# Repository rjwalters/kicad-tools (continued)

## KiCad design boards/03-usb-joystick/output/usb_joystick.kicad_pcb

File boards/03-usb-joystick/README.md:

# USB Joystick Controller Demo

This demo demonstrates the kicad-tools autorouter by routing a USB game controller PCB
with mixed signal types: USB differential pairs, analog inputs, and digital I/O.

## Quick Start

```bash
# One-command build (recommended)
kct build boards/03-usb-joystick

# Or run specific steps
kct build boards/03-usb-joystick --step schematic
kct build boards/03-usb-joystick --step pcb
kct build boards/03-usb-joystick --step route
kct build boards/03-usb-joystick --step verify

# Preview what would happen
kct build boards/03-usb-joystick --dry-run
```

## Circuit Overview

```
                          +------------------+
    +--------+            |                  |
    | USB-C  |---D+/D--->| MCU (32-pin QFP) |<---[Y1 Crystal]
    |  J1    |---VBUS--->|                  |
    +--------+            |   ATmega32U4    |<---[C1-C4 Decoupling]
                          |                  |
                          +--------+---------+
                                   |
          +------------------------+------------------------+
          |            |           |           |            |
      +---+---+   +----+----+  +---+---+   +---+---+   +---+---+
      | JOY_X |   | JOY_Y   |  | BTN1  |   | BTN2  |   | BTN3  |
      +-------+   +---------+  +-------+   +-------+   +-------+
         Analog Joystick              Tactile Buttons
```

## Components

| Reference | Description | Footprint |
|-----------|-------------|-----------|
| U1 | Microcontroller (ATmega32U4-style) | TQFP-32 7x7mm |
| J1 | USB Type-C Connector | USB-C Receptacle |
| J2 | 2-axis Analog Joystick | 5-pin module |
| SW1-SW4 | Tactile Buttons | 6x6mm SMD |
| Y1 | 16MHz Crystal | HC49 Vertical |
| C1-C4 | Decoupling Capacitors (100nF) | 0402 SMD |

## Signal Types

This design demonstrates routing of different signal classes:

### USB Signals (High Priority)
- **USB_D+, USB_D-**: Differential pair, should be length-matched
- **VBUS**: 5V power from USB host
- **USB_CC1, USB_CC2**: Configuration channel for USB-C

### Analog Signals
- **JOY_X, JOY_Y**: Analog joystick axis outputs (0-VCC)
- **JOY_BTN**: Joystick button (active low)

### Digital Signals
- **BTN1-BTN4**: Button inputs (active low with GND)
- **XTAL1, XTAL2**: Crystal oscillator connections

### Power
- **VCC**: 3.3V/5V regulated power
- **GND**: Ground reference
- **VBUS**: USB 5V input

## Files

| File | Description |
|------|-------------|
| `generate_pcb.py` | Script to generate the unrouted PCB file |
| `generate_schematic.py` | Script to generate the schematic file |
| `route_demo.py` | Thin wrapper that delegates to `generate_design.py:route_pcb()` (Issue #3308) |
| `generate_design.py` | End-to-end design flow (schematic + PCB + route + export); owns the canonical routing recipe |
| `output/usb_joystick.kicad_sch` | Generated schematic |
| `output/usb_joystick.kicad_pcb` | Generated unrouted PCB |
| `output/usb_joystick_routed.kicad_pcb` | Routed PCB output |

## Advanced: Manual Build

For more control over individual steps, you can run Python scripts directly. See [Prerequisites](../README.md#prerequisites-for-manual-build) for environment setup.

### Step 1: Generate the Schematic

```bash
# From repository root (default output)
uv run python boards/03-usb-joystick/generate_schematic.py

# Or specify an output directory (auto-appends filename)
uv run python boards/03-usb-joystick/generate_schematic.py output/

# Or specify an explicit file path
uv run python boards/03-usb-joystick/generate_schematic.py output/usb_joystick.kicad_sch
```

Creates `output/usb_joystick.kicad_sch` with all components and wiring.

### Step 2: Generate the PCB

```bash
# From repository root
uv run python boards/03-usb-joystick/generate_pcb.py
```

Creates `output/usb_joystick.kicad_pcb` with all components placed and nets defined.

### Step 3: Run the Autorouter

```bash
# From repository root
uv run python boards/03-usb-joystick/route_demo.py
```

Issue #3308 (June 2026): `route_demo.py` is a thin wrapper that
delegates to `generate_design.py:route_pcb()`.  This guarantees the
demo recipe and the end-to-end build recipe share a single
implementation -- they cannot drift again.  `kct build --step route`
also invokes `route_demo.py` (see `_run_step_route` in
`src/kicad_tools/cli/build_cmd.py`), so all three entry points
(``route_demo.py``, ``kct build --step route``, ``generate_design.py``)
now produce the same routed output.

This:
1. Loads the unrouted PCB
2. Configures net classes (USB gets high priority)
3. Routes signal nets (power nets are skipped, assuming planes)
4. Saves the result to `output/usb_joystick_routed.kicad_pcb`

**Note:** This is a challenging routing problem with a dense 32-pin QFP and multiple
signal types. The autorouter demonstrates its capabilities but may not complete all
routes on a 2-layer board. This is realistic for complex designs requiring manual
intervention or additional layers.

### Step 4: View in KiCad (Optional)

Open `usb_joystick_routed.kicad_pcb` in KiCad to visualize the routes.

## Net Class Configuration

The demo configures net classes for priority-based routing:

```python
net_class_map = create_net_class_map(
    power_nets=["VCC", "VBUS", "GND"],  # Highest priority
    high_speed_nets=["USB_D+", "USB_D-"],  # USB differential pair
    clock_nets=["XTAL1", "XTAL2"],  # Crystal oscillator
)
```

This ensures:
1. Power nets route first (if not skipped)
2. USB differential pair routes early for best path
3. Crystal traces stay short
4. Button/joystick signals route last

## Design Considerations

### USB Routing
- D+ and D- should be routed as a differential pair
- Keep traces short and matched in length
- Avoid sharp bends (use 45-degree angles)

### Analog Signals
- JOY_X and JOY_Y carry analog voltages
- Keep away from high-speed digital signals
- Consider guard traces if noise is an issue

### Crystal Routing
- XTAL1 and XTAL2 should be short
- Place crystal close to MCU pins
- Avoid routing other signals under crystal

### Decoupling Capacitors
- C1-C3 placed close to MCU VCC pins
- C4 on VBUS near USB connector
- Short traces to GND plane

## Customization

### Change Design Rules

```python
rules = DesignRules(
    grid_resolution=0.25,  # Routing grid
    trace_width=0.25,  # Default trace width
    trace_clearance=0.15,  # Minimum clearance
    via_drill=0.3,  # Via drill diameter
    via_diameter=0.6,  # Via pad diameter
)
```

### Route Power Nets

By default, VCC/GND/VBUS are skipped (assuming copper pours). To route them:

```python
skip_nets = []  # Route everything
```

### Adjust Component Placement

Edit `generate_pcb.py` to modify:
- Board dimensions
- Component positions
- Pin assignments

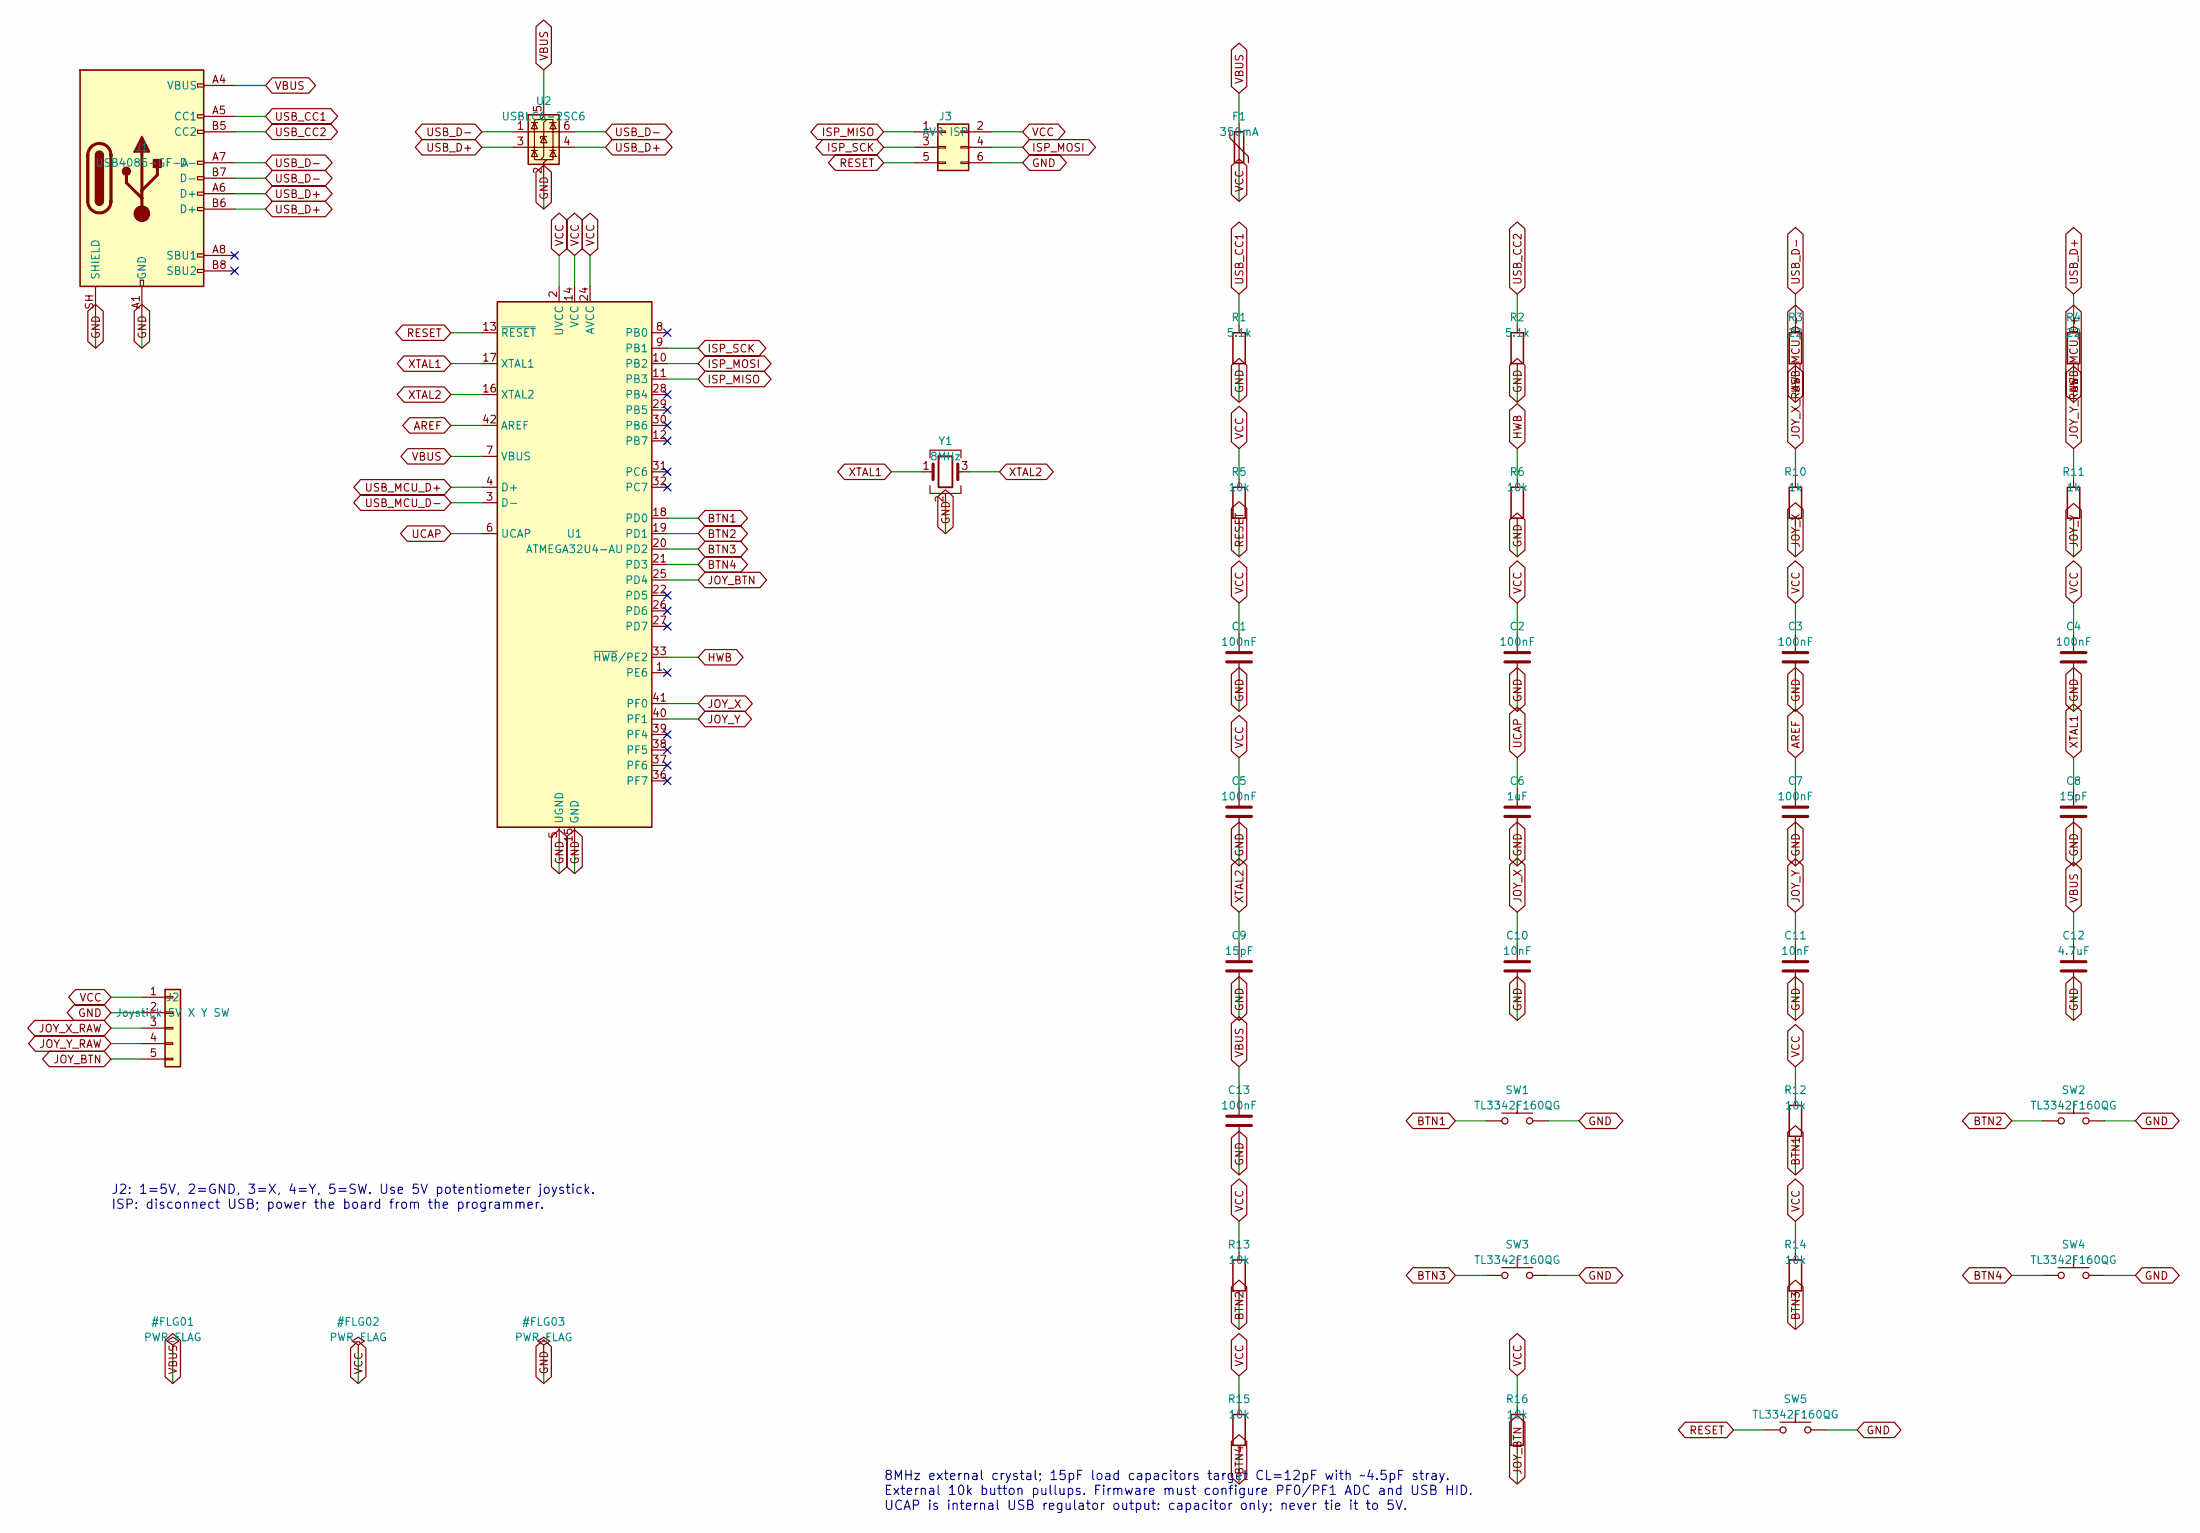
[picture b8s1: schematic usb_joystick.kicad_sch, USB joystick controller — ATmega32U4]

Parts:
C1, C2, C3, C4, C5, C7, C13: 100nF; C_0603_1608Metric; MPN GRM188R71C104KA01D; LCSC C45000
C6: 1uF; C_0603_1608Metric; MPN GRM188R71A105KA61D; LCSC C97888
C8, C9: 15pF; C_0603_1608Metric; MPN GRM1885C1H150JA01D; LCSC C71651
C10, C11: 10nF; C_0603_1608Metric; MPN GRM188R71H103KA01D; LCSC C77053
C12: 4.7uF; C_0603_1608Metric; MPN GRM188R61A475KE15D; LCSC C71633
F1: 350mA; Fuse_1206_3216Metric; MPN 1206L035/16YR; LCSC C126817
J1: USB4085-GF-A; USB_C_Receptacle_GCT_USB4085; MPN USB4085-GF-A; LCSC C7095263
J2: Joystick 5V X Y SW; JST_PH_S5B-PH-SM4-TB_1x05-1MP_P2.00mm_Horizontal; MPN S5B-PH-SM4-TB(LF)(SN); LCSC C265104
J3: AVR ISP; Samtec_TSM-103-01-T-DV; MPN TSM-103-01-T-DV-P-TR; LCSC C21285200
R1, R2: 5.1k; R_0603_1608Metric; MPN RC0603FR-075K1L; LCSC C105580
R3, R4: 22; R_0402_1005Metric; MPN RC0402FR-0722RL; LCSC C114765
R5, R6, R12, R13, R14, R15, R16: 10k; R_0603_1608Metric; MPN RC0603FR-0710KL; LCSC C98220
R10, R11: 1k; R_0603_1608Metric; MPN RC0603FR-071KL; LCSC C22548
SW1, SW2, SW3, SW4, SW5: TL3342F160QG; SW_SPST_TL3342; MPN TL3342F160QG; LCSC C2886898
U1: ATMEGA32U4-AU; TQFP-44_10x10mm_P0.8mm; MPN ATMEGA32U4-AU; LCSC C44854
U2: USBLC6-2SC6; SOT-23-6; MPN USBLC6-2SC6; LCSC C7519
Y1: 8MHz; Crystal_SMD_3225-4Pin_3.2x2.5mm; MPN ECS-80-12-33-JGN-TR; LCSC C2442665

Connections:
AREF: C7.1, U1.42 (AREF)
BTN1: R12.2, SW1.1, U1.18 (PD0)
BTN2: R13.2, SW2.1, U1.19 (PD1)
BTN3: R14.2, SW3.1, U1.20 (PD2)
BTN4: R15.2, SW4.1, U1.21 (PD3)
GND: C1.2, C2.2, C3.2, C4.2, C5.2, C6.2, C7.2, C8.2, C9.2, C10.2, C11.2, C12.2, C13.2, J1.A1 (GND), J1.A12 (GND), J1.B1 (GND), J1.B12 (GND), J1.SH (SHIELD), J2.2, J3.6, R1.2, R2.2, R6.2, SW1.2, SW2.2, SW3.2, SW4.2, SW5.2, U1.5 (UGND), U1.15 (GND), U1.23 (GND), U1.35 (GND), U1.43 (GND), U2.2 (GND), Y1.2 (G), Y1.4 (G)
HWB: R6.1, U1.33 (~HWB/PE2)
ISP_MISO: J3.1, U1.11 (PB3)
ISP_MOSI: J3.4, U1.10 (PB2)
ISP_SCK: J3.3, U1.9 (PB1)
JOY_BTN: J2.5, R16.2, U1.25 (PD4)
JOY_X: C10.1, R10.2, U1.41 (PF0)
JOY_X_RAW: J2.3, R10.1
JOY_Y: C11.1, R11.2, U1.40 (PF1)
JOY_Y_RAW: J2.4, R11.1
RESET: J3.5, R5.2, SW5.1, U1.13 (~RESET)
UCAP: C6.1, U1.6 (UCAP)
USB_CC1: J1.A5 (CC1), R1.1
USB_CC2: J1.B5 (CC2), R2.1
USB_D+: J1.A6 (D+), J1.B6 (D+), R4.1, U2.3 (I/O2), U2.4 (I/O2)
USB_D-: J1.A7 (D-), J1.B7 (D-), R3.1, U2.1 (I/O1), U2.6 (I/O1)
USB_MCU_D+: R4.2, U1.4 (D+)
USB_MCU_D-: R3.2, U1.3 (D-)
VBUS: C12.1, C13.1, F1.1, J1.A4 (VBUS), J1.A9 (VBUS), J1.B4 (VBUS), J1.B9 (VBUS), U1.7 (VBUS), U2.5 (VBUS)
VCC: C1.1, C2.1, C3.1, C4.1, C5.1, F1.2, J2.1, J3.2, R5.1, R12.1, R13.1, R14.1, R15.1, R16.1, U1.2 (UVCC), U1.14 (VCC), U1.24 (AVCC), U1.34 (VCC), U1.44 (AVCC)
XTAL1: C8.1, U1.17 (XTAL1), Y1.1
XTAL2: C9.1, U1.16 (XTAL2), Y1.3

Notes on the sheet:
J2: 1=5V, 2=GND, 3=X, 4=Y, 5=SW. Use 5V potentiometer joystick. ISP: disconnect USB; power the board from the programmer.
8MHz external crystal; 15pF load capacitors target CL=12pF with ~4.5pF stray. External 10k button pullups. Firmware must configure PF0/PF1 ADC and USB HID. UCAP is internal USB regulator output: capacitor only; never tie it to 5V.

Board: 4 copper layers, 38 parts (0 on the bottom side), 27 nets, no tracks yet.

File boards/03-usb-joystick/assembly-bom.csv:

Reference,Value,Manufacturer,MPN,Footprint
U1,ATMEGA32U4-AU,Microchip,ATMEGA32U4-AU,Package_QFP:TQFP-44_10x10mm_P0.8mm
J1,USB4085-GF-A,GCT,USB4085-GF-A,Connector_USB:USB_C_Receptacle_GCT_USB4085
U2,USBLC6-2SC6,STMicroelectronics,USBLC6-2SC6,Package_TO_SOT_SMD:SOT-23-6
F1,350mA,Littelfuse,1206L035/16YR,Fuse:Fuse_1206_3216Metric
Y1,8MHz,ECS,ECS-80-12-33-JGN-TR,Crystal:Crystal_SMD_3225-4Pin_3.2x2.5mm
J2,Joystick 5V X Y SW,JST,S5B-PH-SM4-TB(LF)(SN),Connector_JST:JST_PH_S5B-PH-SM4-TB_1x05-1MP_P2.00mm_Horizontal
J3,AVR ISP,Samtec,TSM-103-01-T-DV-P-TR,Joystick:Samtec_TSM-103-01-T-DV
R1,5.1k,Yageo,RC0603FR-075K1L,Resistor_SMD:R_0603_1608Metric
R2,5.1k,Yageo,RC0603FR-075K1L,Resistor_SMD:R_0603_1608Metric
R3,22,Yageo,RC0402FR-0722RL,Resistor_SMD:R_0402_1005Metric
R4,22,Yageo,RC0402FR-0722RL,Resistor_SMD:R_0402_1005Metric
R5,10k,Yageo,RC0603FR-0710KL,Resistor_SMD:R_0603_1608Metric
R6,10k,Yageo,RC0603FR-0710KL,Resistor_SMD:R_0603_1608Metric
R10,1k,Yageo,RC0603FR-071KL,Resistor_SMD:R_0603_1608Metric
R11,1k,Yageo,RC0603FR-071KL,Resistor_SMD:R_0603_1608Metric
C1,100nF,Murata,GRM188R71C104KA01D,Capacitor_SMD:C_0603_1608Metric
C2,100nF,Murata,GRM188R71C104KA01D,Capacitor_SMD:C_0603_1608Metric
C3,100nF,Murata,GRM188R71C104KA01D,Capacitor_SMD:C_0603_1608Metric
C4,100nF,Murata,GRM188R71C104KA01D,Capacitor_SMD:C_0603_1608Metric
C5,100nF,Murata,GRM188R71C104KA01D,Capacitor_SMD:C_0603_1608Metric
C6,1uF,Murata,GRM188R71A105KA61D,Capacitor_SMD:C_0603_1608Metric
C7,100nF,Murata,GRM188R71C104KA01D,Capacitor_SMD:C_0603_1608Metric
C8,15pF,Murata,GRM1885C1H150JA01D,Capacitor_SMD:C_0603_1608Metric
C9,15pF,Murata,GRM1885C1H150JA01D,Capacitor_SMD:C_0603_1608Metric
C10,10nF,Murata,GRM188R71H103KA01D,Capacitor_SMD:C_0603_1608Metric
C11,10nF,Murata,GRM188R71H103KA01D,Capacitor_SMD:C_0603_1608Metric
C12,4.7uF,Murata,GRM188R61A475KE15D,Capacitor_SMD:C_0603_1608Metric
C13,100nF,Murata,GRM188R71C104KA01D,Capacitor_SMD:C_0603_1608Metric
SW1,TL3342F160QG,E-Switch,TL3342F160QG,Button_Switch_SMD:SW_SPST_TL3342
R12,10k,Yageo,RC0603FR-0710KL,Resistor_SMD:R_0603_1608Metric
SW2,TL3342F160QG,E-Switch,TL3342F160QG,Button_Switch_SMD:SW_SPST_TL3342
R13,10k,Yageo,RC0603FR-0710KL,Resistor_SMD:R_0603_1608Metric
SW3,TL3342F160QG,E-Switch,TL3342F160QG,Button_Switch_SMD:SW_SPST_TL3342
R14,10k,Yageo,RC0603FR-0710KL,Resistor_SMD:R_0603_1608Metric
SW4,TL3342F160QG,E-Switch,TL3342F160QG,Button_Switch_SMD:SW_SPST_TL3342
R15,10k,Yageo,RC0603FR-0710KL,Resistor_SMD:R_0603_1608Metric
R16,10k,Yageo,RC0603FR-0710KL,Resistor_SMD:R_0603_1608Metric
SW5,TL3342F160QG,E-Switch,TL3342F160QG,Button_Switch_SMD:SW_SPST_TL3342
